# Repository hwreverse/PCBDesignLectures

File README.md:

# PCBDesignLectures
PCB Design course projects

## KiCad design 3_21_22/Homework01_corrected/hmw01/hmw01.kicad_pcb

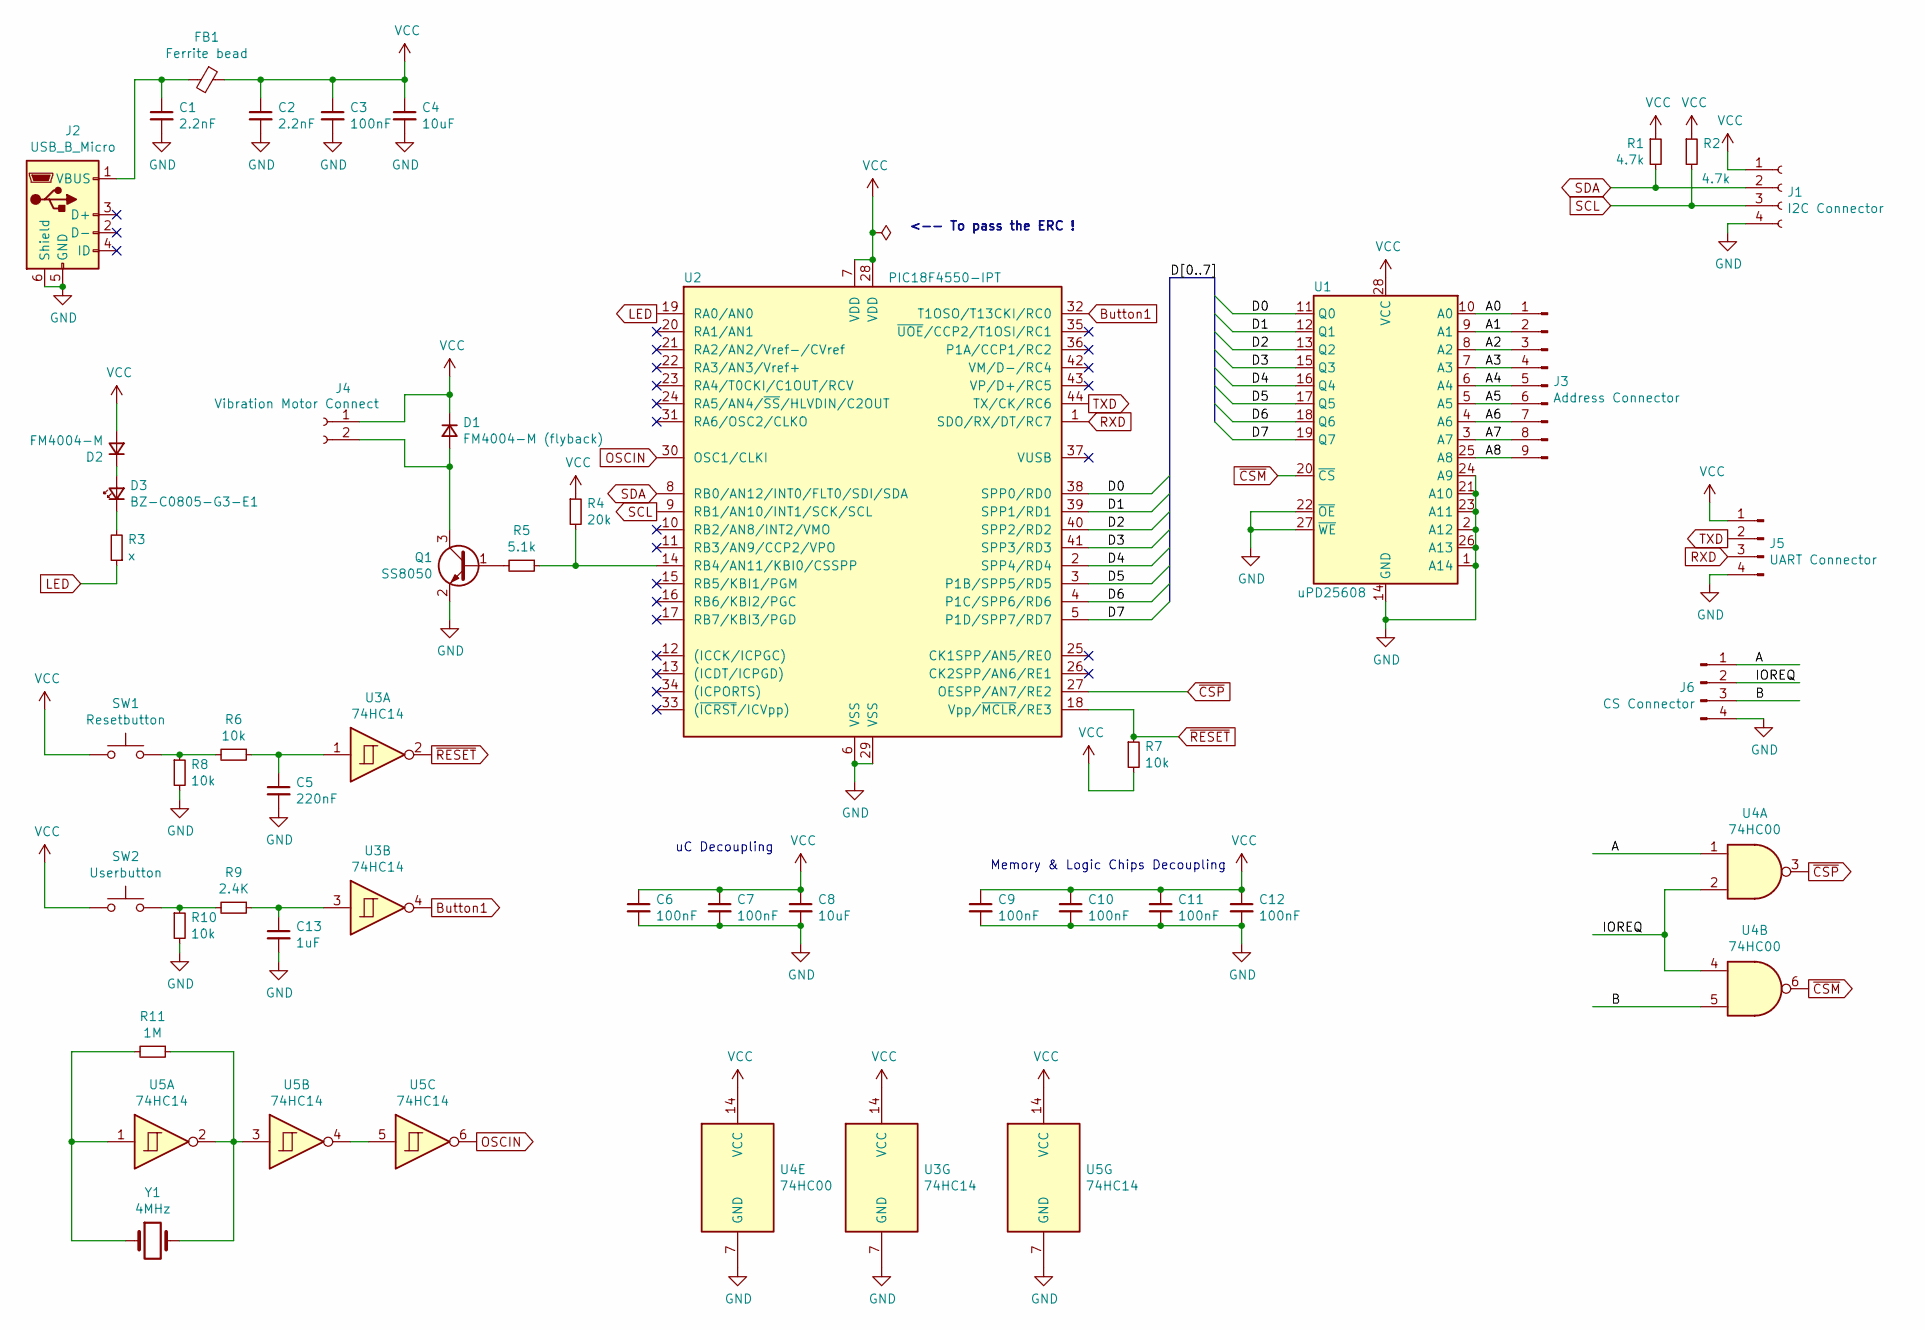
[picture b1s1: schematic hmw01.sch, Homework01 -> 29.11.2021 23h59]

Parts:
C1, C2: 2.2nF; C_0805_2012Metric; LCSC C28260
C3, C6, C7, C9, C10, C11, C12: 100nF; C_0805_2012Metric; LCSC C49678
C4, C8: 10uF; C_0805_2012Metric; LCSC C15850
C5: 220nF; C_0805_2012Metric
C13: 1uF; C_0805_2012Metric; LCSC C28323
D1: FM4004-M (flyback); D_SOD-123
D2: FM4004-M; D_SOD-123
D3: BZ-C0805-G3-E1; LED_0805_2012Metric
FB1: Ferrite bead; L_0805_2012Metric
J1: I2C Connector; PinSocket_1x04_P1.27mm_Vertical
J2: USB_B_Micro; USB_Micro-B_Molex-105017-0001
J3: Address Connector; PinHeader_1x09_P2.54mm_Vertical
J4: Vibration Motor Connect; PinSocket_1x02_P2.00mm_Vertical
J5: UART Connector; PinHeader_1x04_P2.54mm_Vertical_SMD_Pin1Left
J6: CS Connector; PinHeader_1x04_P2.54mm_Vertical_SMD_Pin1Left
Q1: SS8050; SOT-23
R1, R2: 4.7k; R_0805_2012Metric; LCSC C17673
R3: x; R_0805_2012Metric
R4: 20k; R_0805_2012Metric; LCSC C4328
R5: 5.1k; R_0805_2012Metric; LCSC C27834
R6, R7, R8, R10: 10k; R_0805_2012Metric; LCSC C17414
R9: 2.4K; R_0805_2012Metric
R11: 1M; R_0805_2012Metric; LCSC C17514
SW1: Resetbutton; SW_PUSH_6mm_H4.3mm
SW2: Userbutton; SW_PUSH_6mm_H4.3mm
U1: uPD25608; SOIC-28W_7.5x17.9mm_P1.27mm
U2: PIC18F4550-IPT; TQFP-44_10x10mm_P0.8mm
U3, U5: 74HC14; SO-14_3.9x8.65mm_P1.27mm
U4: 74HC00; SO-14_3.9x8.65mm_P1.27mm
Y1: 4MHz; Crystal_HC49-4H_Vertical

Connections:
/A: J6.1, U4.1
/A0: J3.1, U1.10 (A0)
/A1: J3.2, U1.9 (A1)
/A2: J3.3, U1.8 (A2)
/A3: J3.4, U1.7 (A3)
/A4: J3.5, U1.6 (A4)
/A5: J3.6, U1.5 (A5)
/A6: J3.7, U1.4 (A6)
/A7: J3.8, U1.3 (A7)
/A8: J3.9, U1.25 (A8)
/B: J6.3, U4.5
/D0: U1.11 (Q0), U2.38 (SPP0/RD0)
/D1: U1.12 (Q1), U2.39 (SPP1/RD1)
/D2: U1.13 (Q2), U2.40 (SPP2/RD2)
/D3: U1.15 (Q3), U2.41 (SPP3/RD3)
/D4: U1.16 (Q4), U2.2 (SPP4/RD4)
/D5: U1.17 (Q5), U2.3 (P1B/SPP5/RD5)
/D6: U1.18 (Q6), U2.4 (P1C/SPP6/RD6)
/D7: U1.19 (Q7), U2.5 (P1D/SPP7/RD7)
/IOREQ: J6.2, U4.2, U4.4
Button1: U2.32 (T1OSO/T13CKI/RC0), U3.4
GND: C1.2, C2.2, C3.2, C4.2, C5.2, C6.2, C7.2, C8.2, C9.2, C10.2, C11.2, C12.2, C13.2, J1.4, J2.5 (GND), J2.6 (Shield), J5.4, J6.4, Q1.2 (E), R8.2, R10.2, U1.1 (A14), U1.2 (A12), U1.14 (GND), U1.21 (A10), U1.22 (~OE), U1.23 (A11), U1.24 (A9), U1.26 (A13), U1.27 (~WE), U2.6 (VSS), U2.29 (VSS), U3.7 (GND), U4.7 (GND), U5.7 (GND)
LED: R3.1, U2.19 (RA0/AN0)
unnamed: C1.1, FB1.2, J2.1 (VBUS)
unnamed: C5.1, R6.1, U3.1
unnamed: C13.1, R9.1, U3.3
unnamed: D1.2 (A), J4.2, Q1.3 (C)
unnamed: D2.1 (K), D3.2 (A)
unnamed: D3.1 (K), R3.2
unnamed: Q1.1 (B), R5.2
unnamed: R4.2, R5.1, U2.14 (RB4/AN11/KBI0/CSSPP)
unnamed: R6.2, R8.1, SW1.2
unnamed: R9.2, R10.1, SW2.2
unnamed: R11.1, U5.2, U5.3, Y1.2
unnamed: R11.2, U5.1, Y1.1
unnamed: U5.4, U5.5
OSCIN: U2.30 (OSC1/CLKI), U5.6
RXD: J5.3, U2.1 (SDO/RX/DT/RC7)
SCL: J1.3, R2.2, U2.9 (RB1/AN10/INT1/SCK/SCL)
SDA: J1.2, R1.2, U2.8 (RB0/AN12/INT0/FLT0/SDI/SDA)
TXD: J5.2, U2.44 (TX/CK/RC6)
VCC: C2.1, C3.1, C4.1, C6.1, C7.1, C8.1, C9.1, C10.1, C11.1, C12.1, D1.1 (K), D2.2 (A), FB1.1, J1.1, J4.1, J5.1, R1.1, R2.1, R4.1, R7.2, SW1.1, SW2.1, U1.28 (VCC), U2.7 (VDD), U2.28 (VDD), U3.14 (VCC), U4.14 (VCC), U5.14 (VCC)
~CSM: U1.20 (~CS), U4.6
~CSP: U2.27 (OESPP/AN7/RE2), U4.3
~RESET: R7.1, U2.18 (Vpp/~MCLR~/RE3), U3.2

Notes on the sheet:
uC Decoupling
Memory & Logic Chips Decoupling
<-- To pass the ERC !

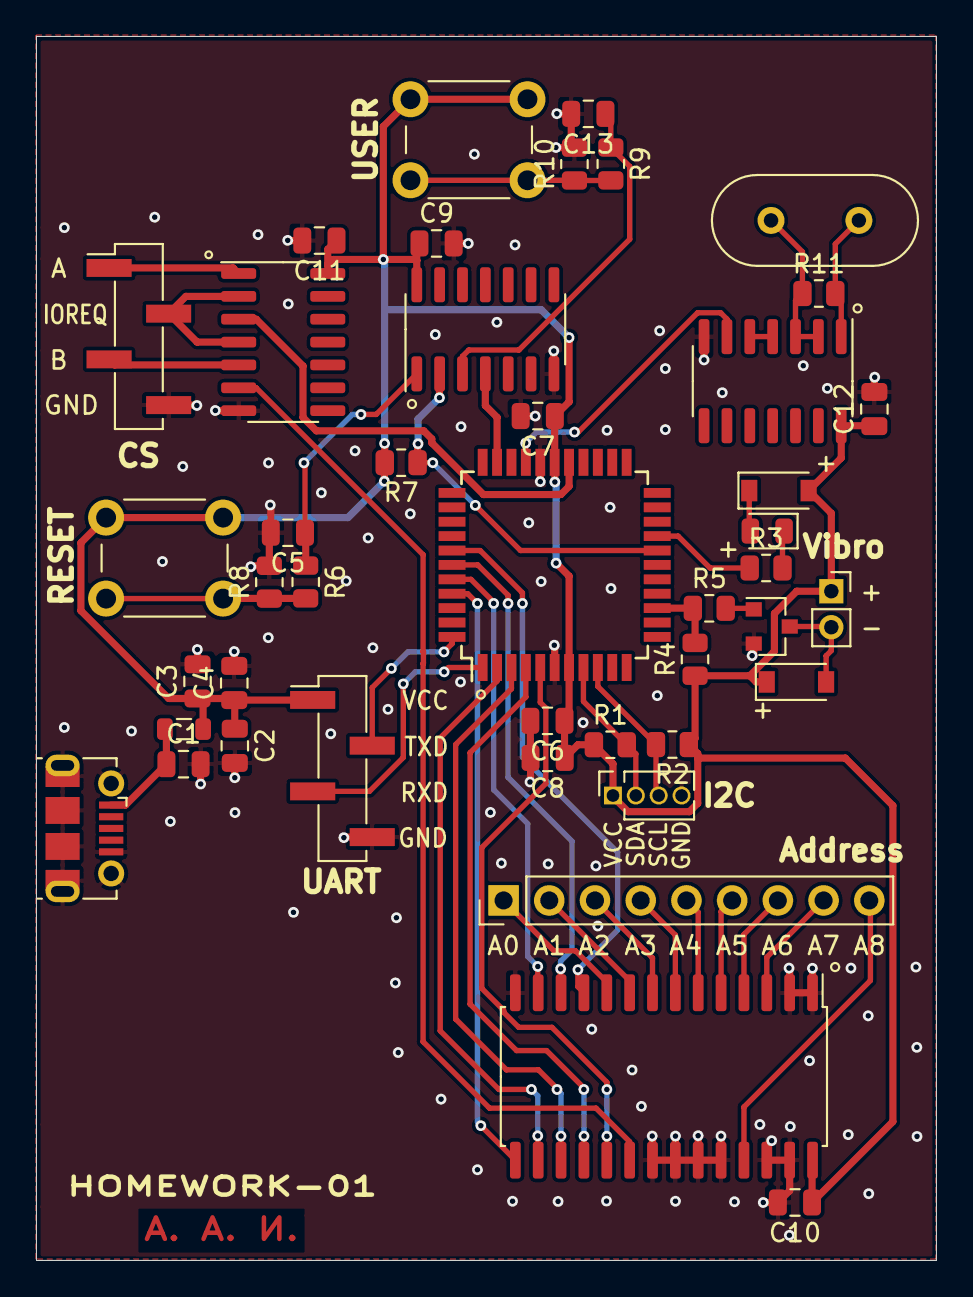
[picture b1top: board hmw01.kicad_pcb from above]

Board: 2 copper layers, 50.0 x 68.0 mm, 43 parts (0 on the bottom side), 45 nets.

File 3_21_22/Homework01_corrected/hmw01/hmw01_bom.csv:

Comment,Designator,Footprint,LCSC
"100nF","C9,C3,C12,C11,C10,C7,C6","C_0805_2012Metric","C49678"
"2.2nF","C2,C1","C_0805_2012Metric","C28260"
"74HC00","U4","Package_SO:SO-14_3.9x8.65mm_P1.27mm",""
"x","R3","R_0805_2012Metric",""
"Resetbutton","SW1","Button_Switch_THT:SW_PUSH_6mm_H4.3mm",""
"Address Connector","J3","Connector_PinHeader_2.54mm:PinHeader_1x09_P2.54mm_Vertical",""
"Vibration Motor Connect","J4","Connector_PinSocket_2.00mm:PinSocket_1x02_P2.00mm_Vertical",""
"USB_B_Micro","J2","Connector_USB:USB_Micro-B_Molex-105017-0001",""
"4.7k","R1,R2","R_0805_2012Metric","C17673"
"74HC14","U5,U3","Package_SO:SO-14_3.9x8.65mm_P1.27mm",""
"I2C Connector","J1","Connector_PinSocket_1.27mm:PinSocket_1x04_P1.27mm_Vertical",""
"5.1k","R5","R_0805_2012Metric","C27834"
"PIC18F4550-IPT","U2","Package_QFP:TQFP-44_10x10mm_P0.8mm",""
"10uF","C8,C4","C_0805_2012Metric","C15850"
"1M","R11","R_0805_2012Metric","C17514"
"10k","R6,R7,R8,R10","R_0805_2012Metric","C17414"
"UART Connector","J5","Connector_PinHeader_2.54mm:PinHeader_1x04_P2.54mm_Vertical_SMD_Pin1Left",""
"Ferrite bead","FB1","Inductor_SMD:L_0805_2012Metric",""
"FM4004-M","D2","Diode_SMD:D_SOD-123",""
"FM4004-M (flyback)","D1","Diode_SMD:D_SOD-123",""
"1uF","C13","C_0805_2012Metric","C28323"
"uPD25608","U1","Package_SO:SOIC-28W_7.5x17.9mm_P1.27mm",""
"220nF","C5","C_0805_2012Metric",""
"CS Connector","J6","Connector_PinHeader_2.54mm:PinHeader_1x04_P2.54mm_Vertical_SMD_Pin1Left",""
"2.4K","R9","R_0805_2012Metric",""
"BZ-C0805-G3-E1","D3","LED_SMD:LED_0805_2012Metric",""
"4MHz","Y1","Crystal:Crystal_HC49-4H_Vertical",""
"SS8050","Q1","Package_TO_SOT_SMD:SOT-23",""
"Userbutton","SW2","Button_Switch_THT:SW_PUSH_6mm_H4.3mm",""
"20k","R4","R_0805_2012Metric","C4328"

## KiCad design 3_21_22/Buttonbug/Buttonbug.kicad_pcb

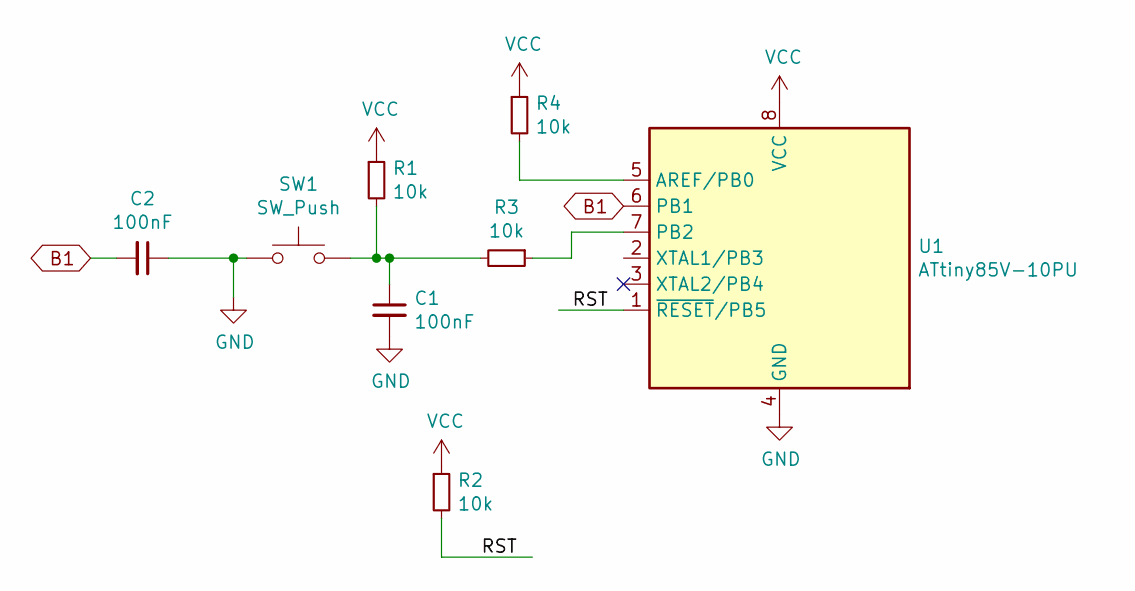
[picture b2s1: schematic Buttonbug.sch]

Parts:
C1, C2: 100nF; C_0402_1005Metric; LCSC C1525
R1, R2, R3, R4: 10k; R_0402_1005Metric; LCSC C25744
SW1: SW_Push; SW_DIP_SPSTx02_Slide_Omron_A6H-2101_W6.15mm_P1.27mm
U1: ATtiny85V-10PU; DIP-8_W7.62mm

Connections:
/RST: R2.2, U1.1 (~RESET~/PB5)
B1: C2.2, U1.6 (PB1)
GND: C1.2, C2.1, SW1.1, U1.4 (GND)
unnamed: C1.1, R1.2, R3.2, SW1.2
unnamed: R3.1, U1.7 (PB2)
unnamed: R4.2, U1.5 (AREF/PB0)
VCC: R1.1, R2.1, R4.1, U1.8 (VCC)

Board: 2 copper layers, 8 parts (0 on the bottom side), 7 nets, no tracks yet.

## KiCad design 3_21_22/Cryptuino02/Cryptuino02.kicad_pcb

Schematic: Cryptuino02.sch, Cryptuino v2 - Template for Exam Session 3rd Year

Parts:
C1: 10nF; C_0402_1005Metric
C2, C5, C6, C7, C11, C12: 100nF; C_0402_1005Metric
C3, C8: 10uF; C_0805_2012Metric
C4: 4.7uF; C_0805_2012Metric
C9, C10: 15pF; C_0603_1608Metric
F1: Polyfuse_Small; Fuse_1206_3216Metric
FB1: 600R @100MHz; L_0805_2012Metric
J1: Interface Connector; PinHeader_1x05_P2.54mm_Horizontal
J2: USB_B_Micro; USB_Micro-B_Molex-105017-0001
R1, R2, R3, R4: 4k7; R_0603_1608Metric
U1: CP2112; QFN-24-1EP_4x4mm_P0.5mm_EP2.6x2.6mm
U2: ATmega88-20MU; QFN-32-1EP_5x5mm_P0.5mm_EP3.1x3.1mm
U3: 74LS02; SSOP-14_5.3x6.2mm_P0.65mm
Y1: 8MHz; Crystal_HC49-4H_Vertical

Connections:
/D0: U1.23 (GPIO.0), U2.30 (PD0)
/D1: U1.22 (GPIO.1), U2.31 (PD1)
/D2: U1.21 (GPIO.2), U2.32 (PD2)
/D3: U1.20 (GPIO.3), U2.1 (PD3)
/D4: U1.15 (GPIO.4), U2.2 (PD4), U3.2
/D5: U1.14 (GPIO.5), U2.9 (PD5), U3.3
/D6: U1.13 (GPIO.6), U2.10 (PD6), U3.5
/D7: U2.11 (PD7), U3.6
/D8: U1.12 (GPIO.7), U3.10
D+: J2.3 (D+), U1.3 (D+)
D-: J2.2 (D-), U1.4 (D-)
GND: C1.1, C2.1, C3.1, C4.1, C5.1, C6.1, C7.1, C8.1, C9.2, C10.2, C11.1, C12.1, J1.5, J2.5 (GND), J2.6 (Shield), U1.2 (GND), U1.25 (GND), U2.3 (GND), U2.5 (GND), U2.21 (GND), U2.33 (GND), U3.7 (GND)
unnamed: C4.2, U1.16 (VPP)
unnamed: F1.1, FB1.2
unnamed: R2.2, U1.9 (~RST)
unnamed: U3.1, U3.8
unnamed: U3.4, U3.9
SCL: J1.3, R3.2, U1.24 (SCL), U2.28 (PC5)
SDA: J1.2, R4.2, U1.1 (SDA), U2.27 (PC4)
VBUS: F1.2, J2.1 (VBUS)
VCC: C1.2, C2.2, C3.2, C5.2, C6.2, C7.2, C8.2, C11.2, C12.2, FB1.1, J1.1, R1.1, R2.1, R3.1, R4.1, U1.5 (VIO), U1.6 (VDD), U1.7 (REGIN), U1.8 (VBUS), U2.4 (VCC), U2.6 (VCC), U2.18 (AVCC), U3.14 (VCC)
XTAL1: C10.1, U2.7 (XTAL1/PB6), Y1.2
XTAL2: C9.1, U2.8 (XTAL2/PB7), Y1.1
~RESET: J1.4, R1.2, U2.29 (~RESET~/PC6)

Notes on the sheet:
Decoupling for uC
Decoupling for Logic & CP2112

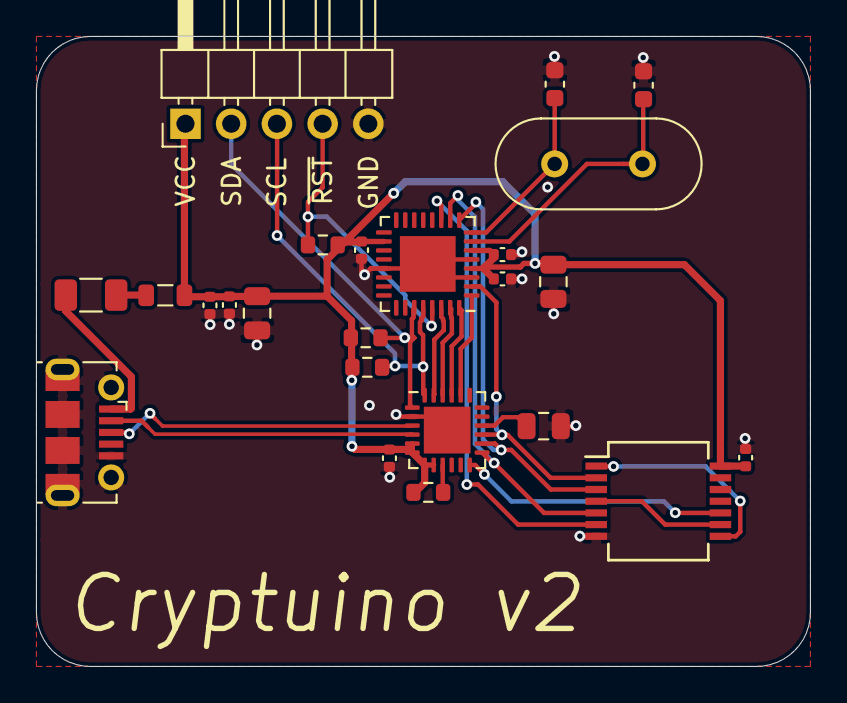
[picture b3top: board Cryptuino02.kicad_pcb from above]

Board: 2 copper layers, 43.0 x 35.0 mm, 24 parts (0 on the bottom side), 24 nets.

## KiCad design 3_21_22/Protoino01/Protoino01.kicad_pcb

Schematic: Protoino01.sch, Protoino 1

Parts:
C1, C2, C4, C7, C9, C10, C11, C17: 100nF; C_0603_1608Metric
C3, C8, C12, C15, C16: 10uF; C_0805_2012Metric
C5, C6: 15pF; C_0603_1608Metric
C13, C14: 1uF; C_0603_1608Metric
D1: PWR_Blue; LED_0603_1608Metric
D2: LED_RED; LED_0603_1608Metric
D3: LED_Yellow; LED_0603_1608Metric
D4: LED_Green; LED_0603_1608Metric
F1: 700mA; Fuse_0603_1608Metric
FB1: Ferrite_Bead_Small; L_0805_2012Metric
H1, H2, H3, H4: MountingHole_Pad; MountingHole_3mm_Pad
J1: USB_C_Receptacle_USB2.0; USB_C_Receptacle_HRO_TYPE-C-31-M-12
J2: ICSP; PinHeader_2x03_P2.54mm_Vertical
J3, J4: Conn_02x06_Odd_Even; PinHeader_2x06_P2.54mm_Vertical
OLED1: I2C_OLED_128x64; OLED_I2C_128x64
R1, R2: 4.7K; R_0603_1608Metric
R3, R4: 5.1K; R_0603_1608Metric
R5: 2.2K; R_0603_1608Metric
R6, R7, R8, R9, R11, R12, R13, R14: 10K; R_0603_1608Metric
R10: 100R; R_0603_1608Metric
R15, R16, R17: ?K; R_0603_1608Metric
SW1: RESET; SW_PUSH_6mm
SW2: SW1; SW_PUSH-12mm
SW3: SW2; SW_PUSH-12mm
U1: ATmega328P-AU; TQFP-32_7x7mm_P0.8mm
U2: CH340C; SOIC-16_3.9x9.9mm_P1.27mm
U3: 74HC14; SOIC-14_3.9x8.7mm_P1.27mm
Y1: 16MHz; Crystal_SMD_3225-4Pin_3.2x2.5mm

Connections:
+5V: C2.1, C3.1, C7.1, C8.1, C9.1, C10.1, C11.1, C17.1, D1.2 (A), D2.2 (A), D3.2 (A), D4.2 (A), FB1.1, J2.2, J3.1, J3.5, J3.9, J4.2, J4.6, J4.10, OLED1.2 (VCC), R1.1, R2.1, R6.2, R7.2, R9.2, R11.2, R12.2, U1.4 (VCC), U1.6 (VCC), U1.18 (AVCC), U2.16 (VCC), U3.14 (VCC)
/IDTR: R10.2, U3.11
/IRES: C12.1, R8.2, U3.1
/S1: C15.1, R13.2, U3.5
/S2: C16.1, R14.2, U3.9
D+: J1.A6 (D+), J1.B6 (D+), U2.5 (UD+)
D-: J1.A7 (D-), J1.B7 (D-), U2.6 (UD-)
DTR: C13.2, U2.13 (~DTR)
GND: C1.2, C2.2, C3.2, C4.2, C5.2, C6.2, C7.2, C8.2, C9.2, C10.2, C11.2, C12.2, C14.1, C15.2, C16.2, C17.2, H1.1, H2.1, H3.1, H4.1, J1.A1 (GND), J1.A12 (GND), J1.B1 (GND), J1.B12 (GND), J1.S1 (SHIELD), J2.6, J3.3, J3.7, J3.11, J4.4, J4.8, J4.12, OLED1.1 (GND), R3.1, R4.1, R5.1, SW1.1, SW2.1, SW3.1, U1.3 (GND), U1.5 (GND), U1.21 (GND), U2.1 (GND), U3.7 (GND), Y1.2, Y1.4
LED1: R15.1, U1.25 (PC2)
LED2: R16.1, U1.24 (PC1)
LED3: R17.1, U1.23 (PC0)
MISO: J2.1, U1.16 (PB4)
MOSI: J2.4, U1.15 (PB3)
unnamed: C1.1, U1.20 (AREF)
unnamed: C4.1, U2.4 (V3)
unnamed: C13.1, C14.2, R9.1, R10.1
unnamed: D1.1 (K), R5.2
unnamed: D2.1 (K), R15.2
unnamed: D3.1 (K), R16.2
unnamed: D4.1 (K), R17.2
unnamed: F1.1, FB1.2
unnamed: F1.2, J1.A4 (VBUS), J1.A9 (VBUS), J1.B4 (VBUS), J1.B9 (VBUS)
unnamed: J1.A5 (CC1), R3.2
unnamed: J1.B5 (CC2), R4.2
unnamed: R6.1, R8.1, SW1.2
unnamed: R11.1, R13.1, SW2.2
unnamed: R12.1, R14.1, SW3.2
unnamed: U3.2, U3.3
unnamed: U3.10, U3.13
OSC1: C5.1, U1.7 (XTAL1/PB6), Y1.1
OSC2: C6.1, U1.8 (XTAL2/PB7), Y1.3
PB0: J3.8, U1.12 (PB0)
PB1: J3.10, U1.13 (PB1)
PB2: J3.12, U1.14 (PB2)
PC3: J4.11, U1.26 (PC3)
PD2: J4.1, U1.32 (PD2)
PD3: J3.2, U1.1 (PD3)
PD4: J3.4, U1.2 (PD4)
PD7: J3.6, U1.11 (PD7)
RXD: J4.5, U1.30 (PD0), U2.2 (TXD)
SCK: J2.3, U1.17 (PB5)
SCL: J4.7, OLED1.3 (SCL), R1.2, U1.28 (PC5)
SDA: J4.9, OLED1.4 (SDA), R2.2, U1.27 (PC4)
SW1: U1.10 (PD6), U3.6
SW2: U1.9 (PD5), U3.8
TXD: J4.3, U1.31 (PD1), U2.3 (RXD)
~RESET: J2.5, R7.1, U1.29 (~RESET~/PC6), U3.4, U3.12

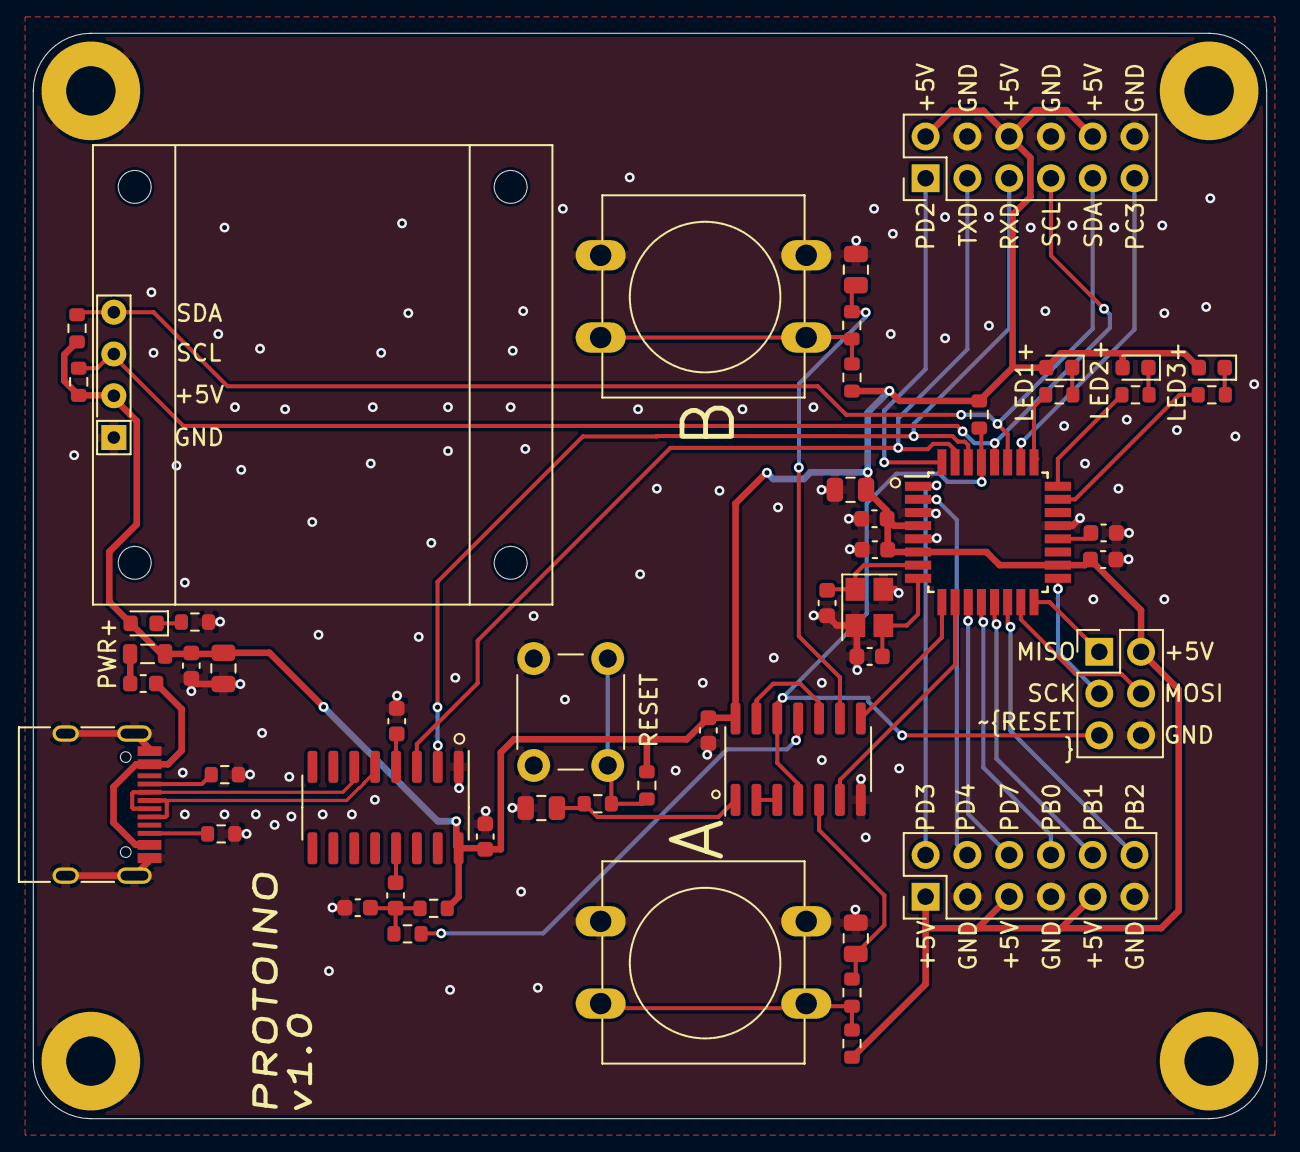
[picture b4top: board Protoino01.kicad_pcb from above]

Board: 2 copper layers, 75.0 x 66.0 mm, 56 parts (0 on the bottom side), 48 nets.

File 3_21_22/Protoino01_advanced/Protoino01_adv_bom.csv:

Comment,Designator,Footprint,LCSC
"15pF","C6,C5","Capacitor_SMD:C_0603_1608Metric",""
"74HC14","U3","Package_SO:SOIC-14_3.9x8.7mm_P1.27mm",""
"4.7K","R1,R2","Resistor_SMD:R_0603_1608Metric",""
"16MHz","Y1","Crystal:Crystal_SMD_3225-4Pin_3.2x2.5mm",""
"MountingHole_Pad","H2,H3,H1,H4","MountingHole:MountingHole_3mm_Pad",""
"Conn_02x06_Odd_Even","J4,J3","Connector_PinHeader_2.54mm:PinHeader_2x06_P2.54mm_Vertical",""
"100nF","C17,C9,C2,C1,C10,C7,C11,C4","Capacitor_SMD:C_0603_1608Metric",""
"ATmega328P-AU","U1","Package_QFP:TQFP-32_7x7mm_P0.8mm",""
"SW1","SW2","Button_Switch_THT:SW_PUSH-12mm",""
"10uF","C3,C12,C8,C16,C15","Capacitor_SMD:C_0805_2012Metric",""
"USB_C_Receptacle_USB2.0","J1","Connector_USB:USB_C_Receptacle_HRO_TYPE-C-31-M-12",""
"RESET","SW1","Button_Switch_THT:SW_PUSH_6mm",""
"LED_RED","D2","LED_SMD:LED_0603_1608Metric",""
"700mA","F1","Fuse:Fuse_0603_1608Metric",""
"2.2K","R5","Resistor_SMD:R_0603_1608Metric",""
"?K","R16,R17,R15","Resistor_SMD:R_0603_1608Metric",""
"5.1K","R4,R3","Resistor_SMD:R_0603_1608Metric",""
"ICSP","J2","Connector_PinHeader_2.54mm:PinHeader_2x03_P2.54mm_Vertical",""
"PWR_Blue","D1","LED_SMD:LED_0603_1608Metric",""
"LED_Green","D4","LED_SMD:LED_0603_1608Metric",""
"LED_Yellow","D3","LED_SMD:LED_0603_1608Metric",""
"CH340C","U2","Package_SO:SOIC-16_3.9x9.9mm_P1.27mm",""
"I2C_OLED_128x64","OLED1","IU10b:OLED_I2C_128x64",""
"Ferrite_Bead_Small","FB1","Inductor_SMD:L_0805_2012Metric",""
"1uF","C13,C14","Capacitor_SMD:C_0603_1608Metric",""
"SW2","SW3","Button_Switch_THT:SW_PUSH-12mm",""
"10K","R6,R7,R12,R13,R11,R8,R14,R9","Resistor_SMD:R_0603_1608Metric",""
"100R","R10","Resistor_SMD:R_0603_1608Metric",""

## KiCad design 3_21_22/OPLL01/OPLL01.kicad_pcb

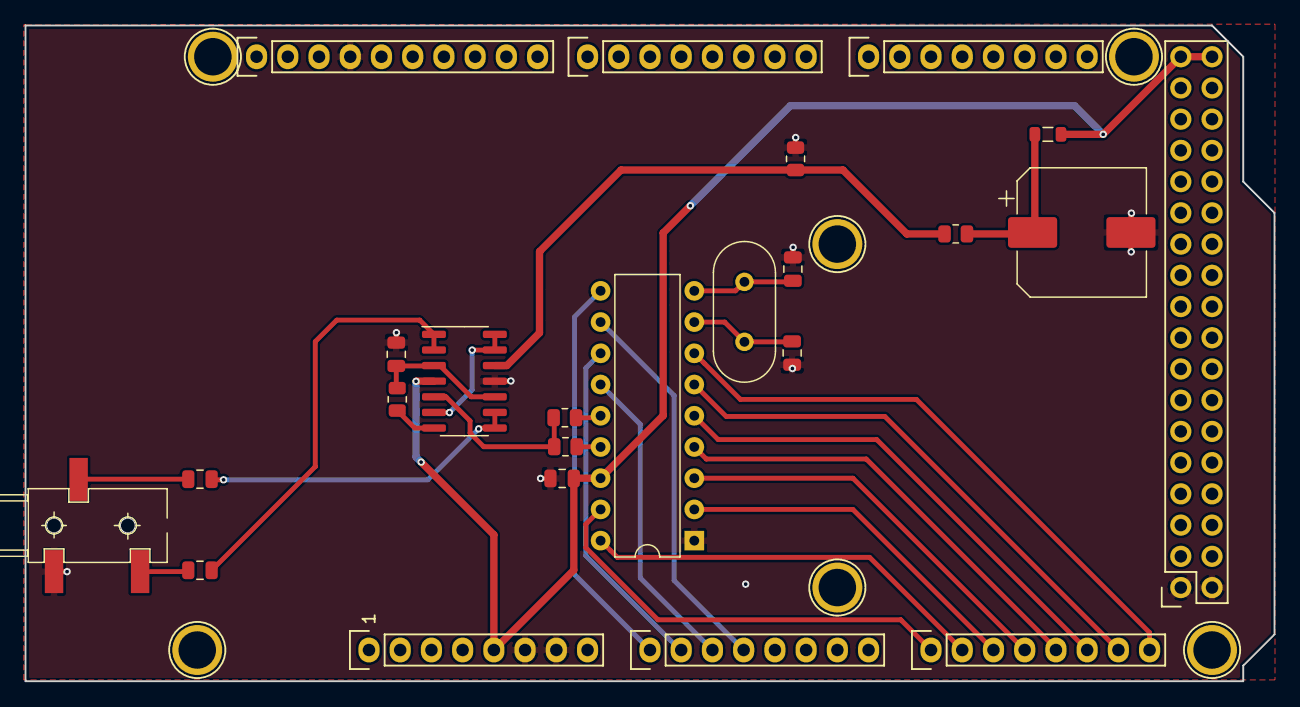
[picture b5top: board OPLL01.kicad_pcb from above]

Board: 2 copper layers, 101.6 x 53.3 mm, 30 parts (0 on the bottom side), 28 nets.

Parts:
C1, C3: 10uF; C_0805_2012Metric
C2: 15nF; C_0805_2012Metric
C4, C5: 15pF; C_0805_2012Metric
C6: 1000uF; CP_Elec_10x10
C7: 100nF; C_0805_2012Metric
J1: AudioJack3; PJ-320B
L1: 1mH; L_0805_2012Metric
P1: Digital; Socket_Strip_Arduino_2x18
P2: Power; Socket_Strip_Arduino_1x08
P3, P4: Analog; Socket_Strip_Arduino_1x08
P5: PWM; Socket_Strip_Arduino_1x10
P6: PWM; Socket_Strip_Arduino_1x08
P7: Communication; Socket_Strip_Arduino_1x08
P8, P9, P10, P11, P12, P13: CONN_01X01; Arduino_1pin
R1, R3: 2k2; R_0805_2012Metric
R2, R5: 4k7; R_0805_2012Metric
R4: 10K; R_0805_2012Metric
U1: LMC660AIM; SOIC-14_3.9x8.7mm_P1.27mm
U2: YM2413; DIP-18_W7.62mm
Y1: 3.57MHz; Crystal_HC49-4H_Vertical

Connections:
+5V: C7.2, L1.1, P1.35, P1.36, P2.5, U1.4, U2.16
/A0: P3.1, U2.10
/D0: P4.1, U2.17
/D1: P4.2, U2.18
/D2: P4.3, U2.2
/D3: P4.4, U2.3
/D4: P4.5, U2.4
/D5: P4.6, U2.5
/D6: P4.7, U2.6
/D7: P4.8, U2.7
/VC: C6.1, L1.2, R4.2
/~CS: P3.2, U2.12
/~IC: P3.3, U2.13
/~WE: P3.4, U2.11
GND: C2.2, C4.1, C5.1, C6.2, C7.1, J1.S, P1.1, P1.2, P2.6, P2.7, P5.4, R5.1, U1.11, U2.1
unnamed: C1.1, J1.T
unnamed: C1.2, U1.1, U1.2
unnamed: C2.1, R2.1, U1.3, U1.10
unnamed: C3.1, J1.R
unnamed: C3.2, U1.8, U1.9
unnamed: C4.2, U2.8, Y1.1
unnamed: C5.2, U2.9, Y1.2
unnamed: R1.1, R3.1, U1.5
unnamed: R1.2, U2.15
unnamed: R2.2, U1.7
unnamed: R3.2, U2.14
unnamed: U1.6, U1.13, U1.14
VREF: R4.1, R5.2, U1.12

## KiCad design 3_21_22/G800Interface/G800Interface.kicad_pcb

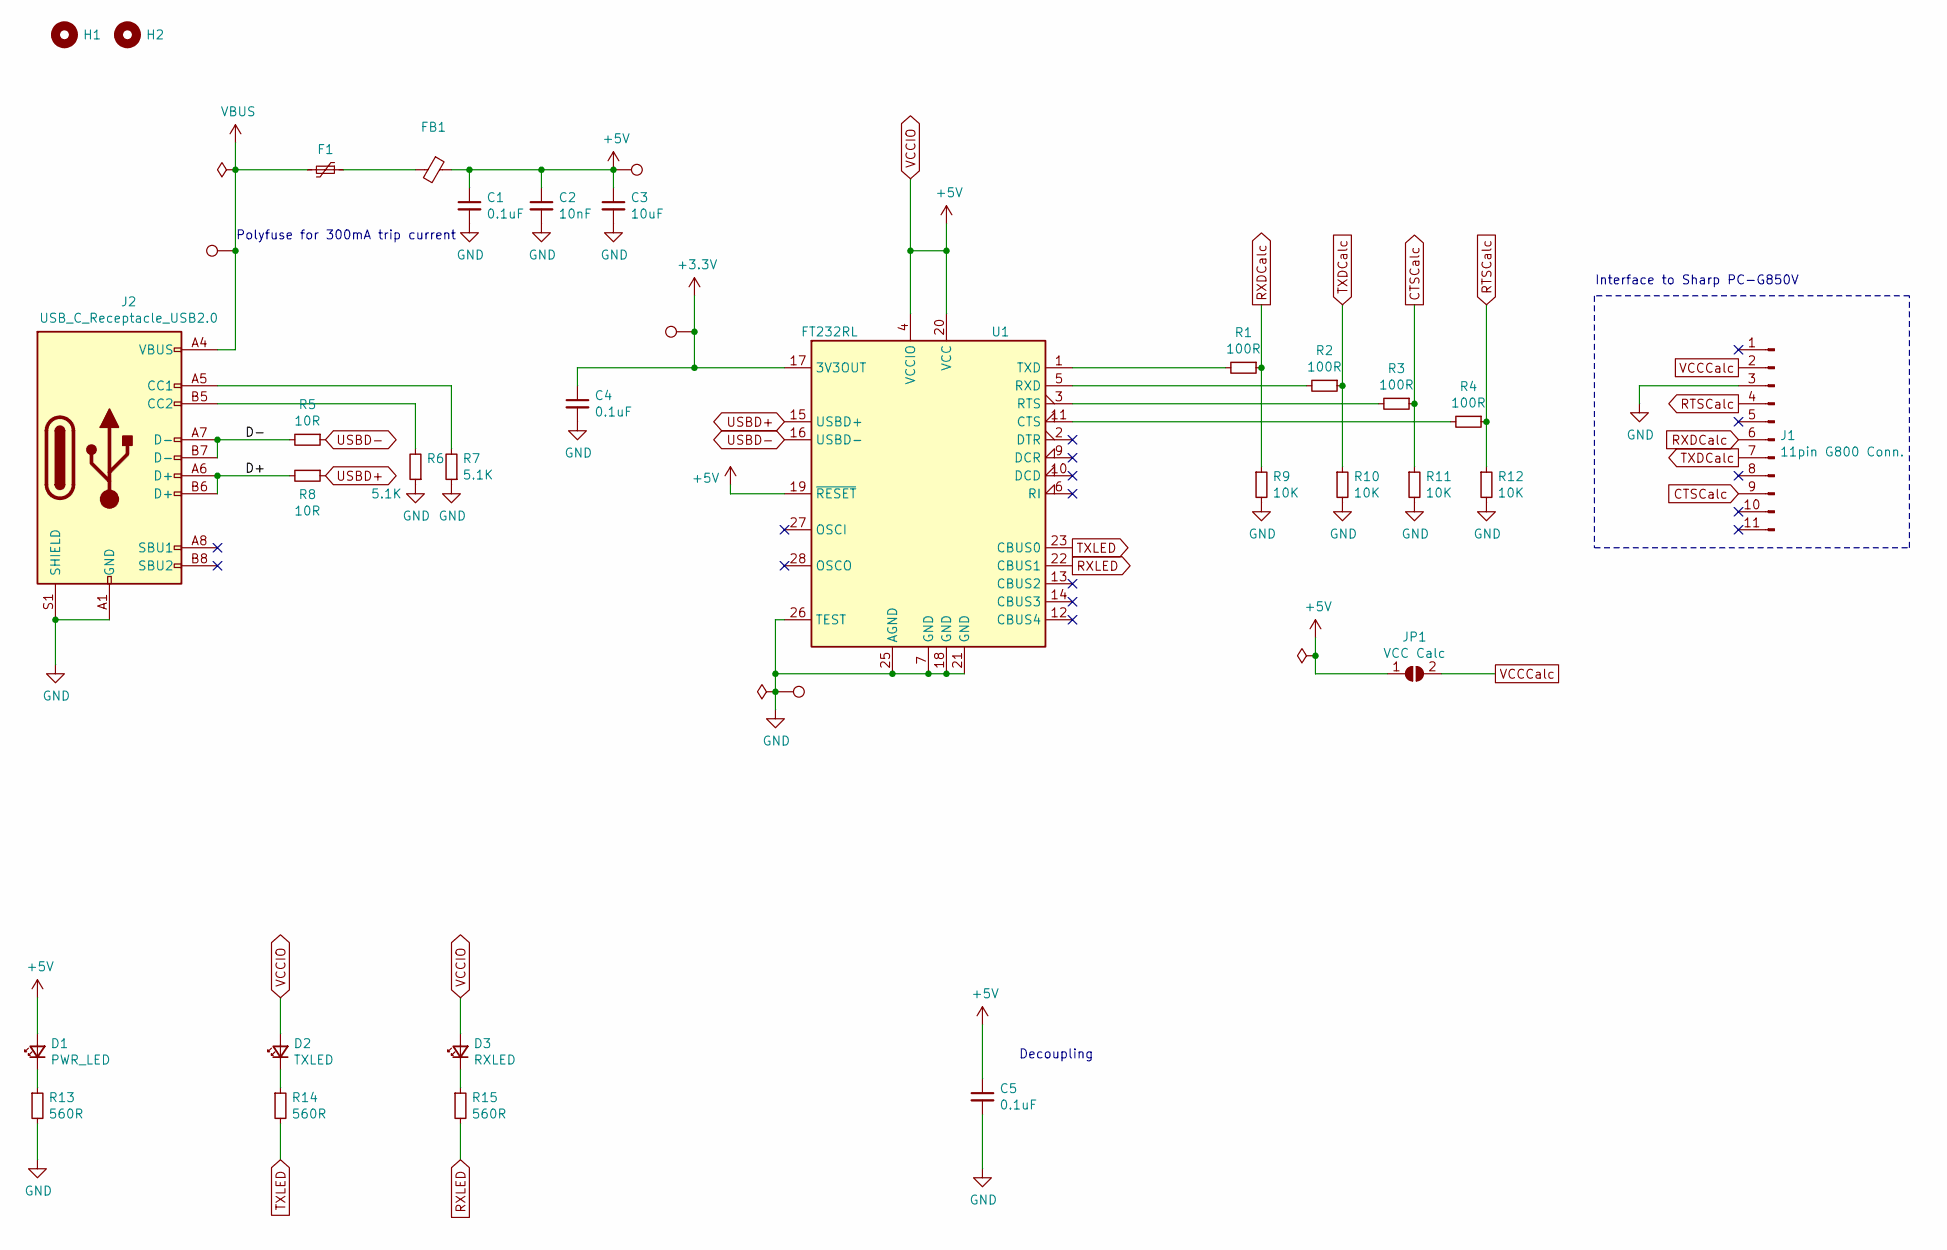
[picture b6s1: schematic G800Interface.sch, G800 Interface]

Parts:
C1, C4, C5: 0.1uF; C_0805_2012Metric
C2: 10nF; C_0805_2012Metric
C3: 10uF; C_0805_2012Metric
D1: PWR_LED; LED_0805_2012Metric
D2: TXLED; LED_0805_2012Metric
D3: RXLED; LED_0805_2012Metric
F1: Polyfuse_Small; Fuse_1812_4532Metric
FB1: Ferrite_Bead_Small; L_0805_2012Metric
H1, H2: MountingHole; MountingHole_3mm
J1: 11pin G800 Conn.; PinHeader_1x11_P2.54mm_Horizontal
J2: USB_C_Receptacle_USB2.0; USB_C_Receptacle_HRO_TYPE-C-31-M-12
JP1: VCC Calc; SolderJumper-2_P1.3mm_Open_RoundedPad1.0x1.5mm
R1, R2, R3, R4: 100R; R_0805_2012Metric
R5, R8: 10R; R_0805_2012Metric
R6, R7: 5.1K; R_0805_2012Metric
R9, R10, R11, R12: 10K; R_0805_2012Metric
R13, R14, R15: 560R; R_0805_2012Metric
TP1: tp5V; TestPoint_Pad_D2.0mm
TP2: tpVBUS; TestPoint_Pad_D2.0mm
TP3: tp3V3; TestPoint_Pad_D2.0mm
TP4: tpGND; TestPoint_Pad_D2.0mm
U1: FT232RL; SSOP-28_5.3x10.2mm_P0.65mm

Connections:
+3V3: C4.1, TP3.1, U1.17 (3V3OUT)
/D+: J2.A6 (D+), J2.B6 (D+), R8.2
/D-: J2.A7 (D-), J2.B7 (D-), R5.2
CTSCalc: J1.9, R3.1, R11.1
GND: C1.2, C2.2, C3.2, C4.2, C5.2, J1.3, J2.A1 (GND), J2.A12 (GND), J2.B1 (GND), J2.B12 (GND), J2.S1 (SHIELD), R6.1, R7.1, R9.2, R10.2, R11.2, R12.2, R13.2, TP4.1, U1.7 (GND), U1.18 (GND), U1.21 (GND), U1.25 (AGND), U1.26 (TEST)
unnamed: D1.1 (K), R13.1
unnamed: D2.1 (K), R14.1
unnamed: D3.1 (K), R15.1
unnamed: F1.1, FB1.2
unnamed: J2.A5 (CC1), R7.2
unnamed: J2.B5 (CC2), R6.2
unnamed: R1.2, U1.1 (TXD)
unnamed: R2.2, U1.5 (RXD)
unnamed: R3.2, U1.3 (RTS)
unnamed: R4.2, U1.11 (CTS)
RTSCalc: J1.4, R4.1, R12.1
RXDCalc: J1.6, R1.1, R9.1
RXLED: R15.2, U1.22 (CBUS1)
TXDCalc: J1.7, R2.1, R10.1
TXLED: R14.2, U1.23 (CBUS0)
USBD+: R8.1, U1.15 (USBD+)
USBD-: R5.1, U1.16 (USBD-)
VBUS: F1.2, J2.A4 (VBUS), J2.A9 (VBUS), J2.B4 (VBUS), J2.B9 (VBUS), TP2.1
VCCCalc: J1.2, JP1.2 (B)
VCCIO: C1.1, C2.1, C3.1, C5.1, D1.2 (A), D2.2 (A), D3.2 (A), FB1.1, JP1.1 (A), TP1.1, U1.4 (VCCIO), U1.19 (~RESET~), U1.20 (VCC)

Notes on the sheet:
Polyfuse for 300mA trip current
Interface to Sharp PC-G850V
Decoupling

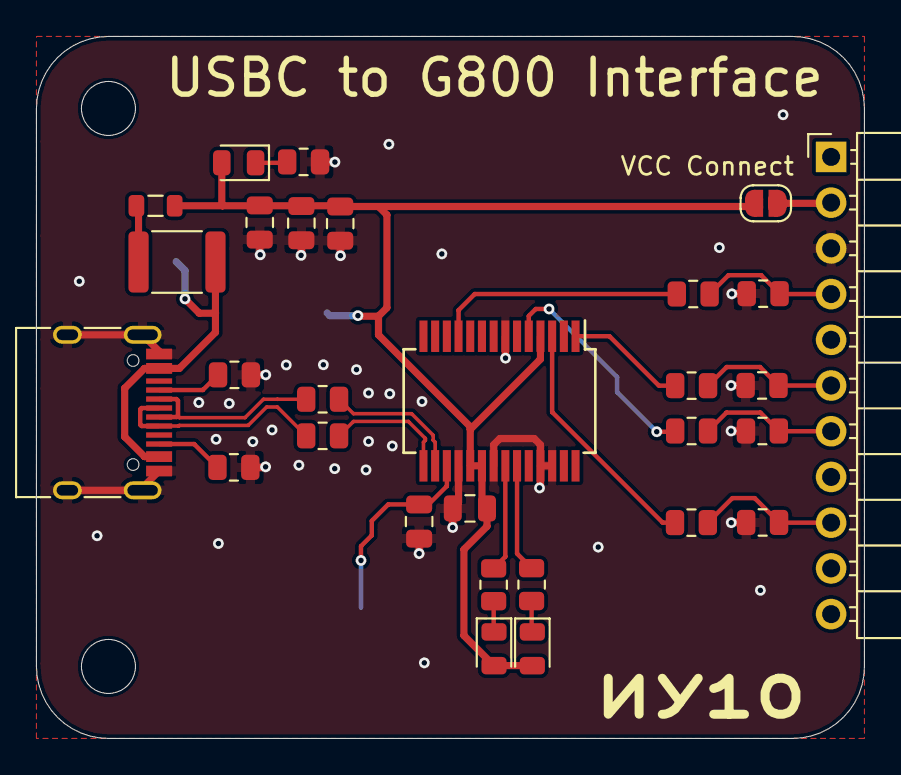
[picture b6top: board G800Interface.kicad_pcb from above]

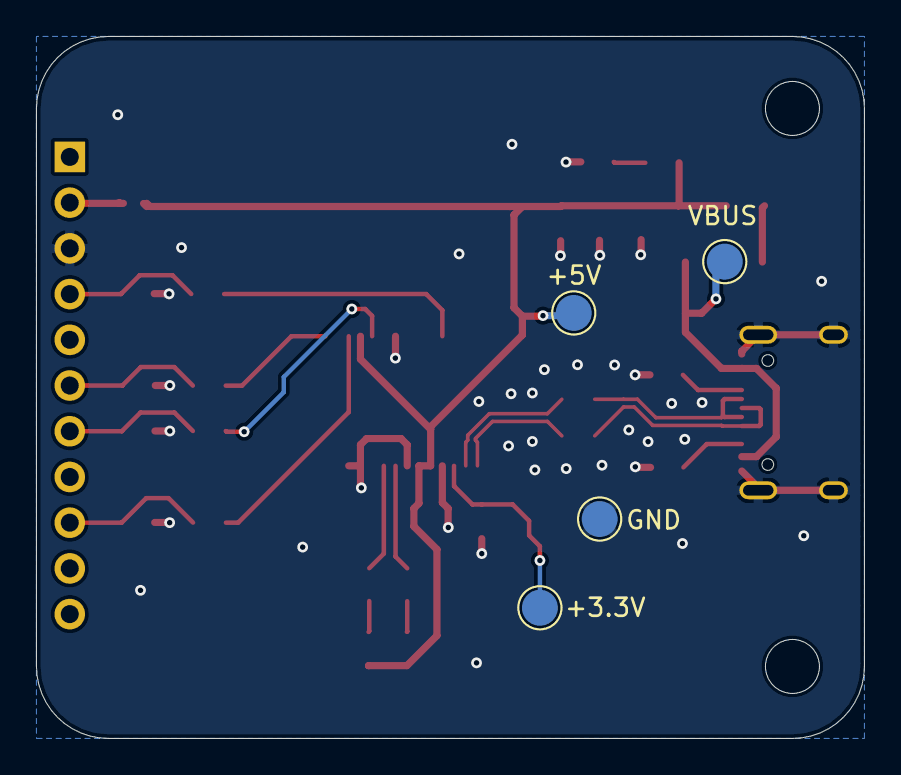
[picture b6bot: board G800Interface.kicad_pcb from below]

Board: 2 copper layers, 46.0 x 39.0 mm, 35 parts (4 on the bottom side), 25 nets.

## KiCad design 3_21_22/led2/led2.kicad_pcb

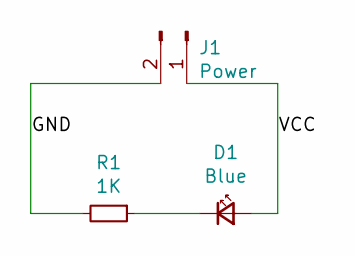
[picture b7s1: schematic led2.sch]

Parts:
D1: Blue; LED_0805_2012Metric
J1: Power; PinHeader_1x02_P2.54mm_Vertical_SMD_Pin1Left
R1: 1K; R_0805_2012Metric

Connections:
/GND: J1.2, R1.2
/VCC: D1.2 (A), J1.1
unnamed: D1.1 (K), R1.1

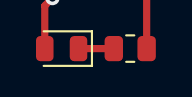
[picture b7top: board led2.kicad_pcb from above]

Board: 2 copper layers, 3 parts (1 on the bottom side), 3 nets.

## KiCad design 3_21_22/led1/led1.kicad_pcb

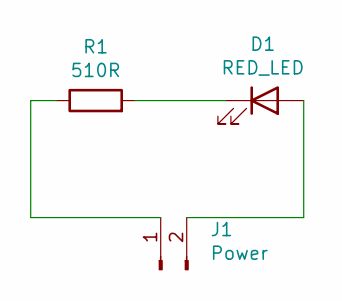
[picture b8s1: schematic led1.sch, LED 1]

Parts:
D1: RED_LED; LED_D5.0mm
J1: Power; PinHeader_1x02_P2.54mm_Vertical
R1: 510R; R_Axial_DIN0207_L6.3mm_D2.5mm_P7.62mm_Horizontal

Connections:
unnamed: D1.1 (K), R1.2
unnamed: D1.2 (A), J1.2
unnamed: J1.1, R1.1

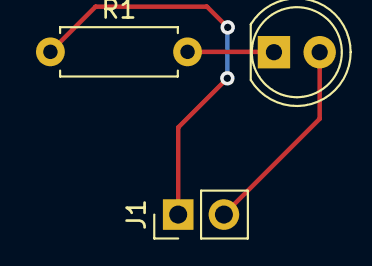
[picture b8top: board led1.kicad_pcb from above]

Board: 2 copper layers, 3 parts (0 on the bottom side), 3 nets.

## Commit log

2021-09-04 added led1
2021-09-09 LED2 Project
2021-09-09 G800 first commit
2021-09-09 Revert "G800 first commit"
    This reverts commit a25ffbeac124ef75fa034ba416c88ae2e06d5b9c.
2021-09-09 Revert "Revert "G800 first commit""
    This reverts commit 28a0679ce1a202f0428d279db196a77ec68eda05.
2021-09-10 Routing G800 Interface
2021-09-16 diff pair + decoupling C
2021-09-17 finished G800
2021-09-24 Added OPLL Arduino Mega Mezzanine
2021-09-30 added PJ-320B datasheet
2021-09-30 Update OPLL
2021-10-01 End of OPLL Project
    finished routing
2021-10-08 added doc
2021-10-08 Protoino01 commit
2021-10-14 sync
2021-10-14 Protoino - 14.10.2021
2021-10-15 protoino 15.10
2021-10-22 Finished Protoino
2021-11-05 Added Gyrolog01
2021-11-10 Added Cryptuino v2
    Added Template for Exam part
2021-11-18 Added 5to12Buck
2021-11-19 finished buck converter
2021-11-25 5to12Boostconverter
2021-11-26 Finished Boostconverter
2021-12-03 Added Homework01_corrected
2021-12-03 Update HMW01
2021-12-04 Added missing ground
